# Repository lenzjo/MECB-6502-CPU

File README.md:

# TLC-6502-CPU for MECB

This is the latest version of my 6502 pcb with several useful additions.

There are 3 sets of pin headers marked with **NMOS** and/or **WDC**. **WDC** refers to Western Digitals 65C02, If you're using that then jumper the pins marked **WDC**, otherwise jumper the **NMOS** marked pins.

This pcb uses a 16Mhz oscillator that is divided down to 1, 2, 4 and 8 Mhz. Jumper the relevant pair of pins for the clock speed you want.

The button's usage is jumper selectable. The **RESET** pin is connected to the reset line and the **PANIC** pin is connected to the **NMI** line. **PANIC** is only useful if your backplane has **Reset** button on it already, like mine. I am currently writing the needed firmware addition to TLCmon. If you are not using TLCmon then you will have to supply the necessary firmware.

The last set of pins (**EEPROM**) allow you to select if the eeprom is in either read or write mode. Under normal usage the **RD** pin should be jumpered.

You may have noticed the socket with double row pins. I have made a 28pin zif socket adapter that has pins spaced at 7.62mm. So on the pcb you use a cheap socket for the inner row of pins. When, if ever ;) , you finish developing your firmware you can solder in two rows of turned pins on the outer rows. I have included the gerbers for the adapter in the **gerbers** directory.

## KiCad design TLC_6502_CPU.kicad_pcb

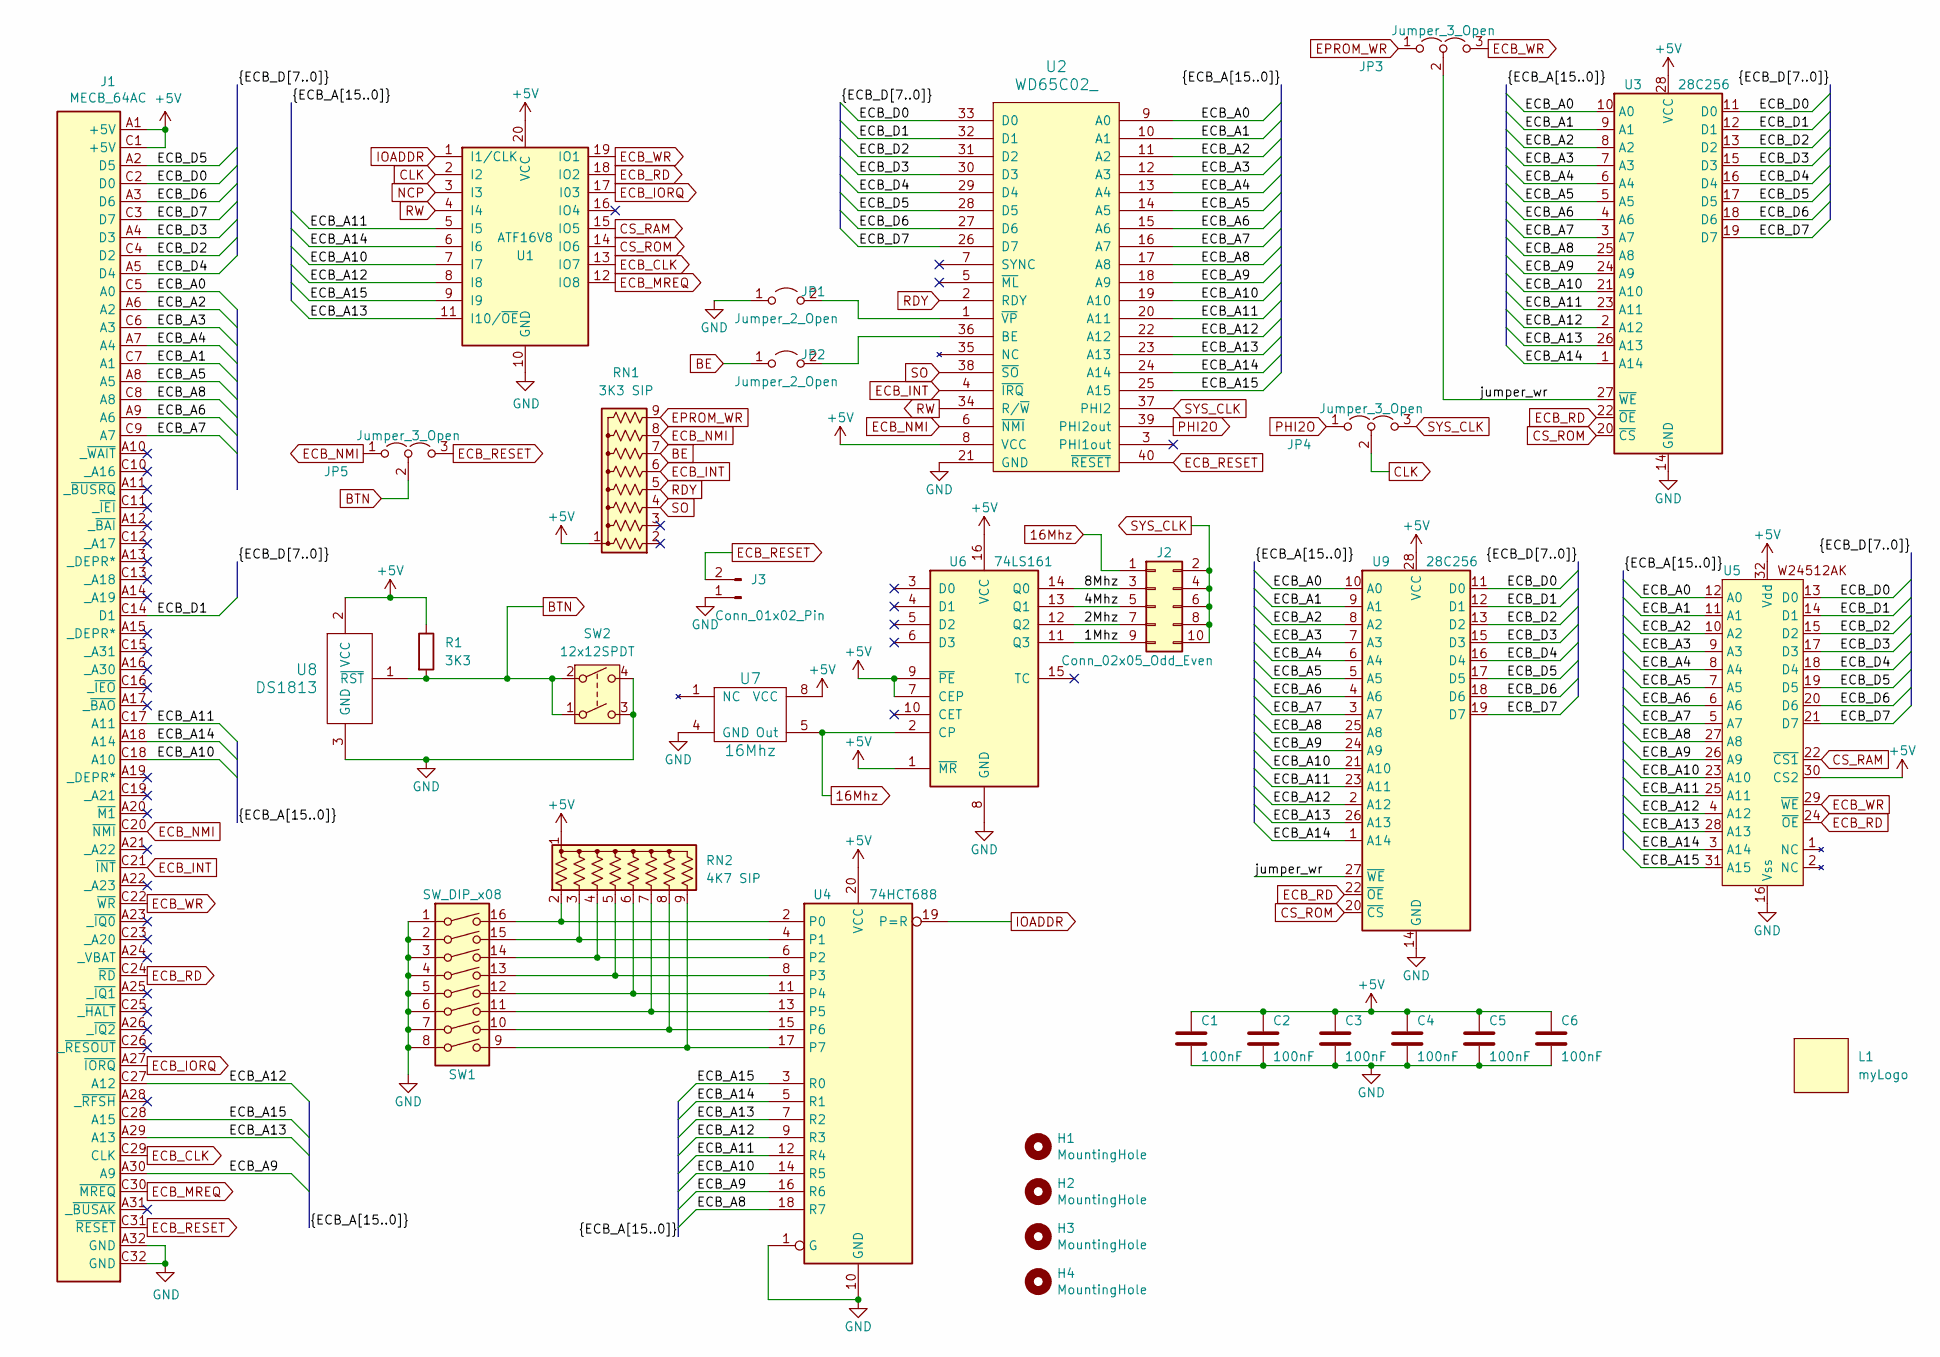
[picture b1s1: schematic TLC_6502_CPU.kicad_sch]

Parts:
C1, C2, C3, C4, C5, C6: 100nF; C_Disc_D7.5mm_W2.5mm_P5.00mm
H1, H2, H3, H4: MountingHole; MountingHole_3.2mm_M3
J1: MECB_64AC; DIN41612_C_2x32_C64AC_Male_Horizontal_THT
J2: Conn_02x05_Odd_Even; PinHeader_2x05_P2.54mm_Vertical
J3: Conn_01x02_Pin; PinHeader_1x02_P2.54mm_Vertical
JP1, JP2: Jumper_2_Open; PinHeader_1x02_P2.54mm_Vertical
JP3, JP4, JP5: Jumper_3_Open; PinHeader_1x03_P2.54mm_Vertical
L1: myLogo; LOGO_sm
R1: 3K3; R_Axial_DIN0309_L9.0mm_D3.2mm_P12.70mm_Horizontal
RN1: 3K3 SIP; R_Array_SIP9
RN2: 4K7 SIP; R_Array_SIP9
SW1: SW_DIP_x08; SW_DIP_SPSTx08_Slide_9.78x22.5mm_W7.62mm_P2.54mm
SW2: 12x12SPDT; 12x12-Tactile-Switch
U1: ATF16V8; DIP-20_W7.62mm_LongPads
U2: WD65C02_; DIP-40_W15.24mm_LongPads
U3: 28C256; DIP-28_W15.24mm_LongPads
U4: 74HCT688; DIP-20_W7.62mm_LongPads
U5: DIP-32_W7.62mm
U6: 74LS161; DIP-16_W7.62mm_LongPads
U7: 16Mhz; 4pinOsc
U8: DS1813; 21-0248A_MXM
U9: 28C256; DIP-28_W7.62mm_Socket_LongPads

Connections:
16Mhz: J2.1, U6.2 (CP), U7.5 (Out)
+5V: C1.1, C2.1, C3.1, C4.1, C5.1, C6.1, J1.A1 (+5V), J1.C1 (+5V), R1.1, RN1.1 (common), RN2.1 (common), U1.20 (VCC), U2.8 (VCC), U3.28 (VCC), U4.20 (VCC), U5.30 (CS2), U5.32 (Vdd), U6.1 (~MR), U6.7 (CEP), U6.9 (~PE), U6.16 (VCC), U7.8 (VCC), U8.2 (VCC), U9.28 (VCC)
/1Mhz: J2.9, U6.11 (Q3)
/2Mhz: J2.7, U6.12 (Q2)
/4Mhz: J2.5, U6.13 (Q1)
/8Mhz: J2.3, U6.14 (Q0)
/ECB_A0: J1.C5 (A0), U2.9 (A0), U3.10 (A0), U5.12 (A0), U9.10 (A0)
/ECB_A1: J1.C7 (A1), U2.10 (A1), U3.9 (A1), U5.11 (A1), U9.9 (A1)
/ECB_A2: J1.A6 (A2), U2.11 (A2), U3.8 (A2), U5.10 (A2), U9.8 (A2)
/ECB_A3: J1.C6 (A3), U2.12 (A3), U3.7 (A3), U5.9 (A3), U9.7 (A3)
/ECB_A4: J1.A7 (A4), U2.13 (A4), U3.6 (A4), U5.8 (A4), U9.6 (A4)
/ECB_A5: J1.A8 (A5), U2.14 (A5), U3.5 (A5), U5.7 (A5), U9.5 (A5)
/ECB_A6: J1.A9 (A6), U2.15 (A6), U3.4 (A6), U5.6 (A6), U9.4 (A6)
/ECB_A7: J1.C9 (A7), U2.16 (A7), U3.3 (A7), U5.5 (A7), U9.3 (A7)
/ECB_A8: J1.C8 (A8), U2.17 (A8), U3.25 (A8), U4.18 (R7), U5.27 (A8), U9.25 (A8)
/ECB_A9: J1.A30 (A9), U2.18 (A9), U3.24 (A9), U4.16 (R6), U5.26 (A9), U9.24 (A9)
/ECB_A10: J1.C18 (A10), U1.7 (I7), U2.19 (A10), U3.21 (A10), U4.14 (R5), U5.23 (A10), U9.21 (A10)
/ECB_A11: J1.C17 (A11), U1.5 (I5), U2.20 (A11), U3.23 (A11), U4.12 (R4), U5.25 (A11), U9.23 (A11)
/ECB_A12: J1.C27 (A12), U1.8 (I8), U2.22 (A12), U3.2 (A12), U4.9 (R3), U5.4 (A12), U9.2 (A12)
/ECB_A13: J1.A29 (A13), U1.11 (I10/~OE), U2.23 (A13), U3.26 (A13), U4.7 (R2), U5.28 (A13), U9.26 (A13)
/ECB_A14: J1.A18 (A14), U1.6 (I6), U2.24 (A14), U3.1 (A14), U4.5 (R1), U5.3 (A14), U9.1 (A14)
/ECB_A15: J1.C28 (A15), U1.9 (I9), U2.25 (A15), U4.3 (R0), U5.31 (A15)
/ECB_D0: J1.C2 (D0), U2.33 (D0), U3.11 (D0), U5.13 (D0), U9.11 (D0)
/ECB_D1: J1.C14 (D1), U2.32 (D1), U3.12 (D1), U5.14 (D1), U9.12 (D1)
/ECB_D2: J1.C4 (D2), U2.31 (D2), U3.13 (D2), U5.15 (D2), U9.13 (D2)
/ECB_D3: J1.A4 (D3), U2.30 (D3), U3.15 (D3), U5.17 (D3), U9.15 (D3)
/ECB_D4: J1.A5 (D4), U2.29 (D4), U3.16 (D4), U5.18 (D4), U9.16 (D4)
/ECB_D5: J1.A2 (D5), U2.28 (D5), U3.17 (D5), U5.19 (D5), U9.17 (D5)
/ECB_D6: J1.A3 (D6), U2.27 (D6), U3.18 (D6), U5.20 (D6), U9.18 (D6)
/ECB_D7: J1.C3 (D7), U2.26 (D7), U3.19 (D7), U5.21 (D7), U9.19 (D7)
/jumper_wr: JP3.2 (C), U3.27 (~WE), U9.27 (~WE)
BE: JP2.1 (A), RN1.7 (R6)
BTN: JP5.2 (C), R1.2, SW2.1, SW2.2, U8.1 (~RST)
CLK: JP4.2 (C), U1.2 (I2)
CS_RAM: U1.15 (IO5), U5.22 (~CS1)
CS_ROM: U1.14 (IO6), U3.20 (~CS), U9.20 (~CS)
ECB_CLK: J1.C29 (CLK), U1.13 (IO7)
ECB_INT: J1.C21 (~INT), RN1.6 (R5), U2.4 (~IRQ)
ECB_IORQ: J1.A27 (~IORQ), U1.17 (I03)
ECB_MREQ: J1.C30 (~MREQ), U1.12 (IO8)
ECB_NMI: J1.C20 (~NMI), JP5.1 (A), RN1.8 (R7), U2.6 (~NMI)
ECB_RD: J1.C24 (~RD), U1.18 (IO2), U3.22 (~OE), U5.24 (~OE), U9.22 (~OE)
ECB_RESET: J1.C31 (~RESET), J3.2, JP5.3 (B), U2.40 (~RESET)
ECB_WR: J1.C22 (~WR), JP3.3 (B), U1.19 (IO1), U5.29 (~WE)
EPROM_WR: JP3.1 (A), RN1.9 (R8)
GND: C1.2, C2.2, C3.2, C4.2, C5.2, C6.2, J1.A32 (GND), J1.C32 (GND), J3.1, JP1.1 (A), SW1.1, SW1.2, SW1.3, SW1.4, SW1.5, SW1.6, SW1.7, SW1.8, SW2.3, SW2.4, U1.10 (GND), U2.21 (GND), U3.14 (GND), U4.1 (G), U4.10 (GND), U5.16 (Vss), U6.8 (GND), U7.4 (GND), U8.3 (GND), U9.14 (GND)
IOADDR: U1.1 (I1/CLK), U4.19 (P=R)
NCP: U1.3 (I3)
unnamed: JP1.2 (B), U2.1 (~VP)
unnamed: JP2.2 (B), U2.36 (BE)
unnamed: RN2.2 (R1), SW1.16, U4.2 (P0)
unnamed: RN2.3 (R2), SW1.15, U4.4 (P1)
unnamed: RN2.4 (R3), SW1.14, U4.6 (P2)
unnamed: RN2.5 (R4), SW1.13, U4.8 (P3)
unnamed: RN2.6 (R5), SW1.12, U4.11 (P4)
unnamed: RN2.7 (R6), SW1.11, U4.13 (P5)
unnamed: RN2.8 (R7), SW1.10, U4.15 (P6)
unnamed: RN2.9 (R8), SW1.9, U4.17 (P7)
PHI2O: JP4.1 (A), U2.39 (PHI2out)
RDY: RN1.5 (R4), U2.2 (RDY)
RW: U1.4 (I4), U2.34 (R/~W)
SO: RN1.4 (R3), U2.38 (~SO)
SYS_CLK: J2.2, J2.4, J2.6, J2.8, J2.10, JP4.3 (B), U2.37 (PHI2)

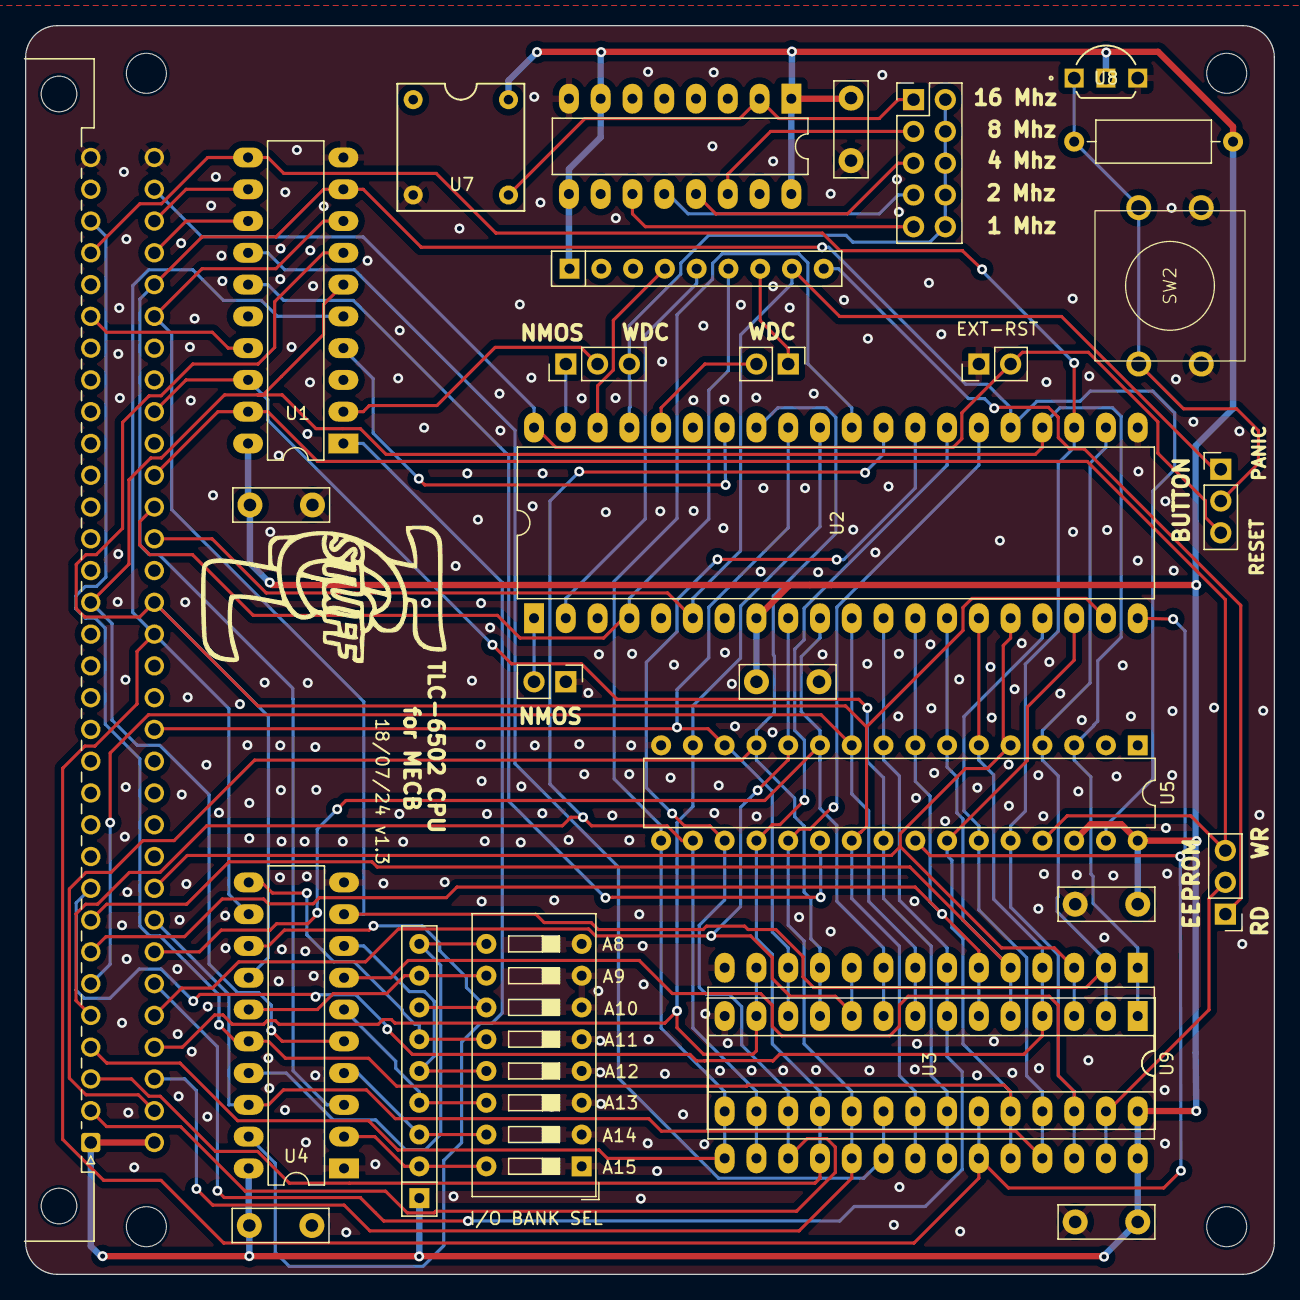
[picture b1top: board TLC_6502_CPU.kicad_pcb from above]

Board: 2 copper layers, 99.8 x 99.8 mm, 33 parts (0 on the bottom side), 62 nets.

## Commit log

2024-07-20 fixed readme ext
